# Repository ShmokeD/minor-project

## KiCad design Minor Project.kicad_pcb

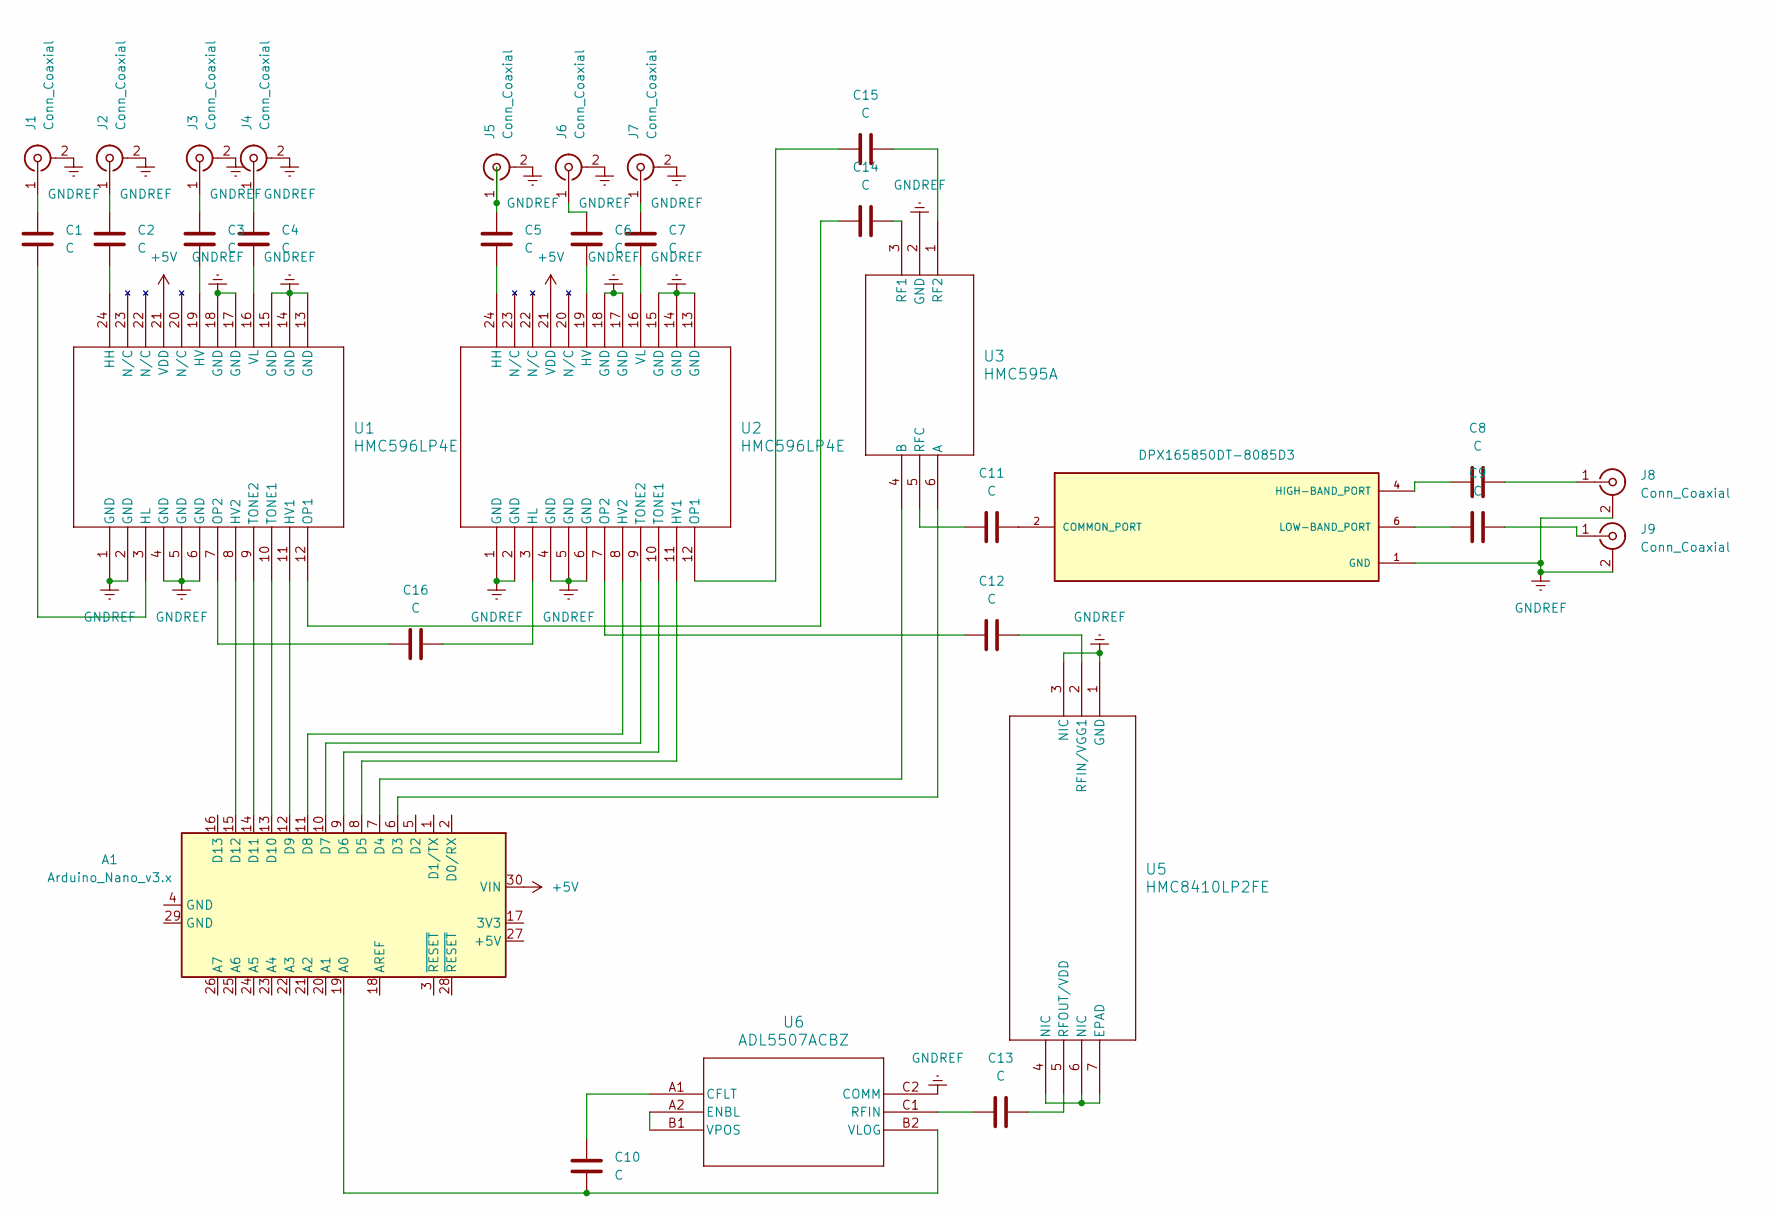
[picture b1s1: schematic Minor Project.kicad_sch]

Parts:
A1: Arduino_Nano_v3.x; Arduino_Nano
C1: C; C_0402_1005Metric_Pad0.74x0.62mm_HandSolder
C2, C3, C4, C5, C6, C7, C8, C9, C10, C11, C12, C13, C14, C15, C16: C; C_0402_1005Metric
J1, J2, J3, J4, J5, J6, J7, J8, J9: Conn_Coaxial; SMA_Molex_73251-1153_EdgeMount_Horizontal
U1, U2: HMC596LP4E; QFN_24_ADI
U3: HMC595A; HMC595A_ADI
U4: DPX165850DT-8085D3; XCVR_DPX165850DT-8085D3
U5: HMC8410LP2FE; CP_6_9_ADI
U6: ADL5507ACBZ; CB-6-14_ADI

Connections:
+5V: A1.30 (VIN), U1.21 (VDD), U2.21 (VDD)
GNDREF: J1.2 (Ext), J2.2 (Ext), J3.2 (Ext), J4.2 (Ext), J5.2 (Ext), J6.2 (Ext), J7.2 (Ext), J8.2 (Ext), J9.2 (Ext), U1.1 (GND), U1.2 (GND), U1.4 (GND), U1.5 (GND), U1.6 (GND), U1.13 (GND), U1.14 (GND), U1.15 (GND), U1.17 (GND), U1.18 (GND), U2.1 (GND), U2.2 (GND), U2.4 (GND), U2.5 (GND), U2.6 (GND), U2.13 (GND), U2.14 (GND), U2.15 (GND), U2.17 (GND), U2.18 (GND), U3.2 (GND), U4.1 (GND), U4.3 (GND), U4.5 (GND), U5.1 (GND), U5.3 (NIC), U6.C2 (COMM)
unnamed: A1.19 (A0), C10.1, U6.B2 (VLOG)
unnamed: A1.6 (D3), U3.6 (A)
unnamed: A1.7 (D4), U3.4 (B)
unnamed: A1.8 (D5), U2.11 (HV1)
unnamed: A1.9 (D6), U2.10 (TONE1)
unnamed: A1.10 (D7), U2.9 (TONE2)
unnamed: A1.11 (D8), U2.8 (HV2)
unnamed: A1.12 (D9), U1.11 (HV1)
unnamed: A1.13 (D10), U1.10 (TONE1)
unnamed: A1.14 (D11), U1.9 (TONE2)
unnamed: A1.15 (D12), U1.8 (HV2)
unnamed: C1.1, J1.1 (In)
unnamed: C2.1, J2.1 (In)
unnamed: C3.1, J3.1 (In)
unnamed: C4.1, J4.1 (In)
unnamed: C5.1, J5.1 (In)
unnamed: C6.1, J6.1 (In)
unnamed: C7.1, J7.1 (In)
unnamed: C8.2, J8.1 (In)
unnamed: C9.2, J9.1 (In)
unnamed: C2.2, U1.24 (HH)
unnamed: C1.2, U1.3 (HL)
unnamed: C3.2, U1.19 (HV)
unnamed: C14.1, U1.12 (OP1)
unnamed: C16.1, U1.7 (OP2)
unnamed: C4.2, U1.16 (VL)
unnamed: C5.2, U2.24 (HH)
unnamed: C16.2, U2.3 (HL)
unnamed: C6.2, U2.19 (HV)
unnamed: C15.1, U2.12 (OP1)
unnamed: C12.1, U2.7 (OP2)
unnamed: C7.2, U2.16 (VL)
unnamed: C14.2, U3.3 (RF1)
unnamed: C15.2, U3.1 (RF2)
unnamed: C11.1, U3.5 (RFC)
unnamed: C11.2, U4.2 (COMMON_PORT)
unnamed: C8.1, U4.4 (HIGH-BAND_PORT)
unnamed: C9.1, U4.6 (LOW-BAND_PORT)
unnamed: U5.4 (NIC), U5.6 (NIC), U5.7 (EPAD)
unnamed: C12.2, U5.2 (RFIN/VGG1)
unnamed: C13.2, U5.5 (RFOUT/VDD)
unnamed: C10.2, U6.A1 (CFLT)
unnamed: U6.A2 (ENBL), U6.B1 (VPOS)
unnamed: C13.1, U6.C1 (RFIN)

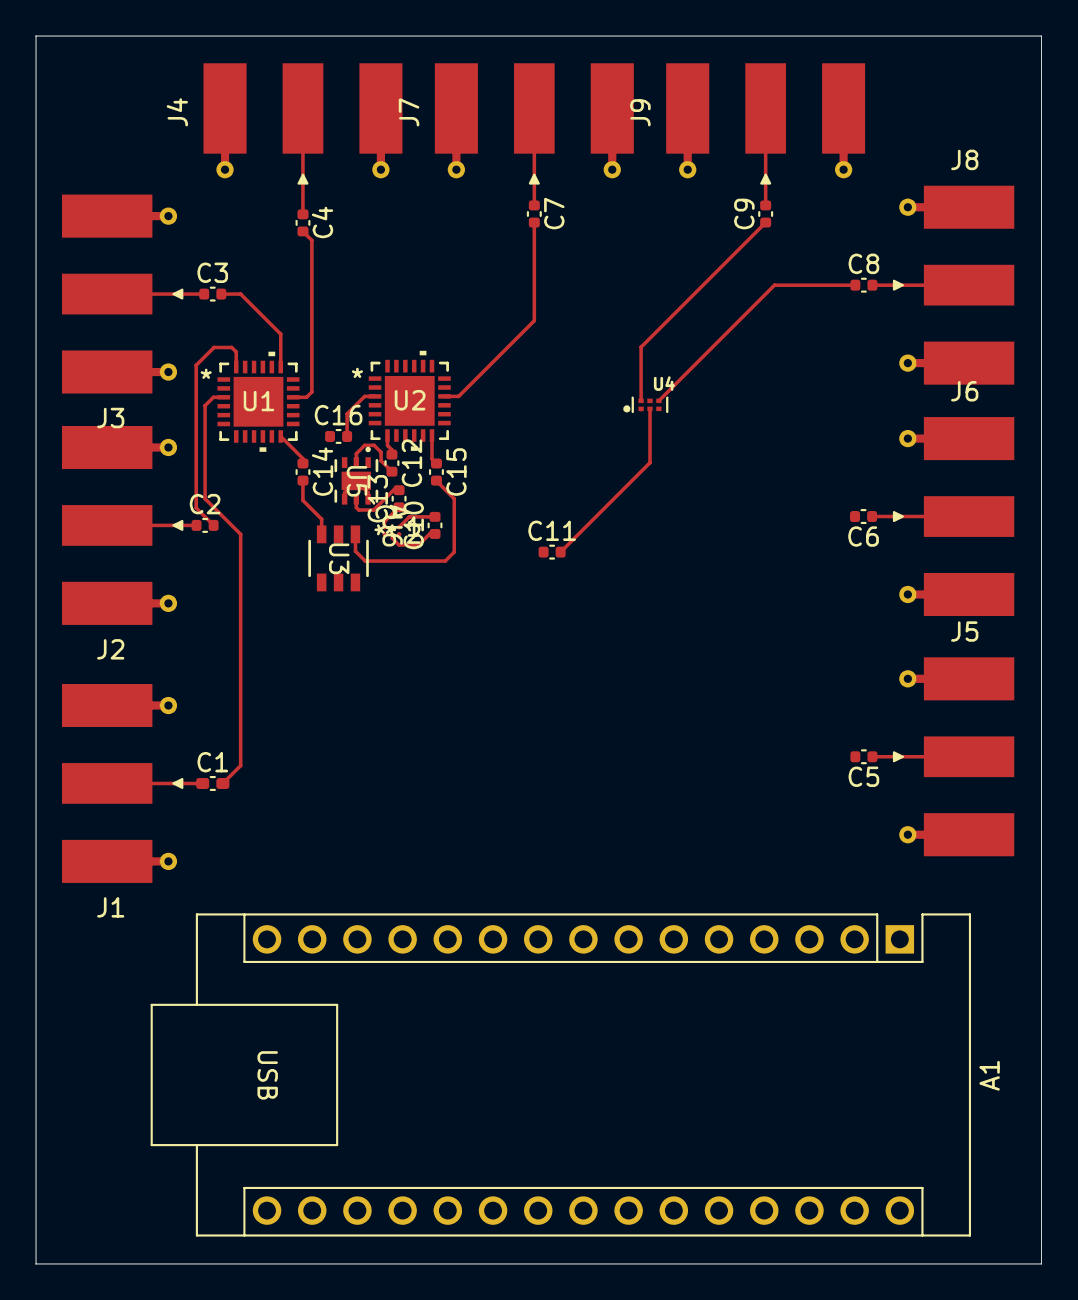
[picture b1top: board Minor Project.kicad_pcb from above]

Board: 2 copper layers, 56.5 x 69.0 mm, 32 parts (0 on the bottom side), 46 nets.

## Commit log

2026-04-15 16 apr
2026-04-16 refactor schematic
